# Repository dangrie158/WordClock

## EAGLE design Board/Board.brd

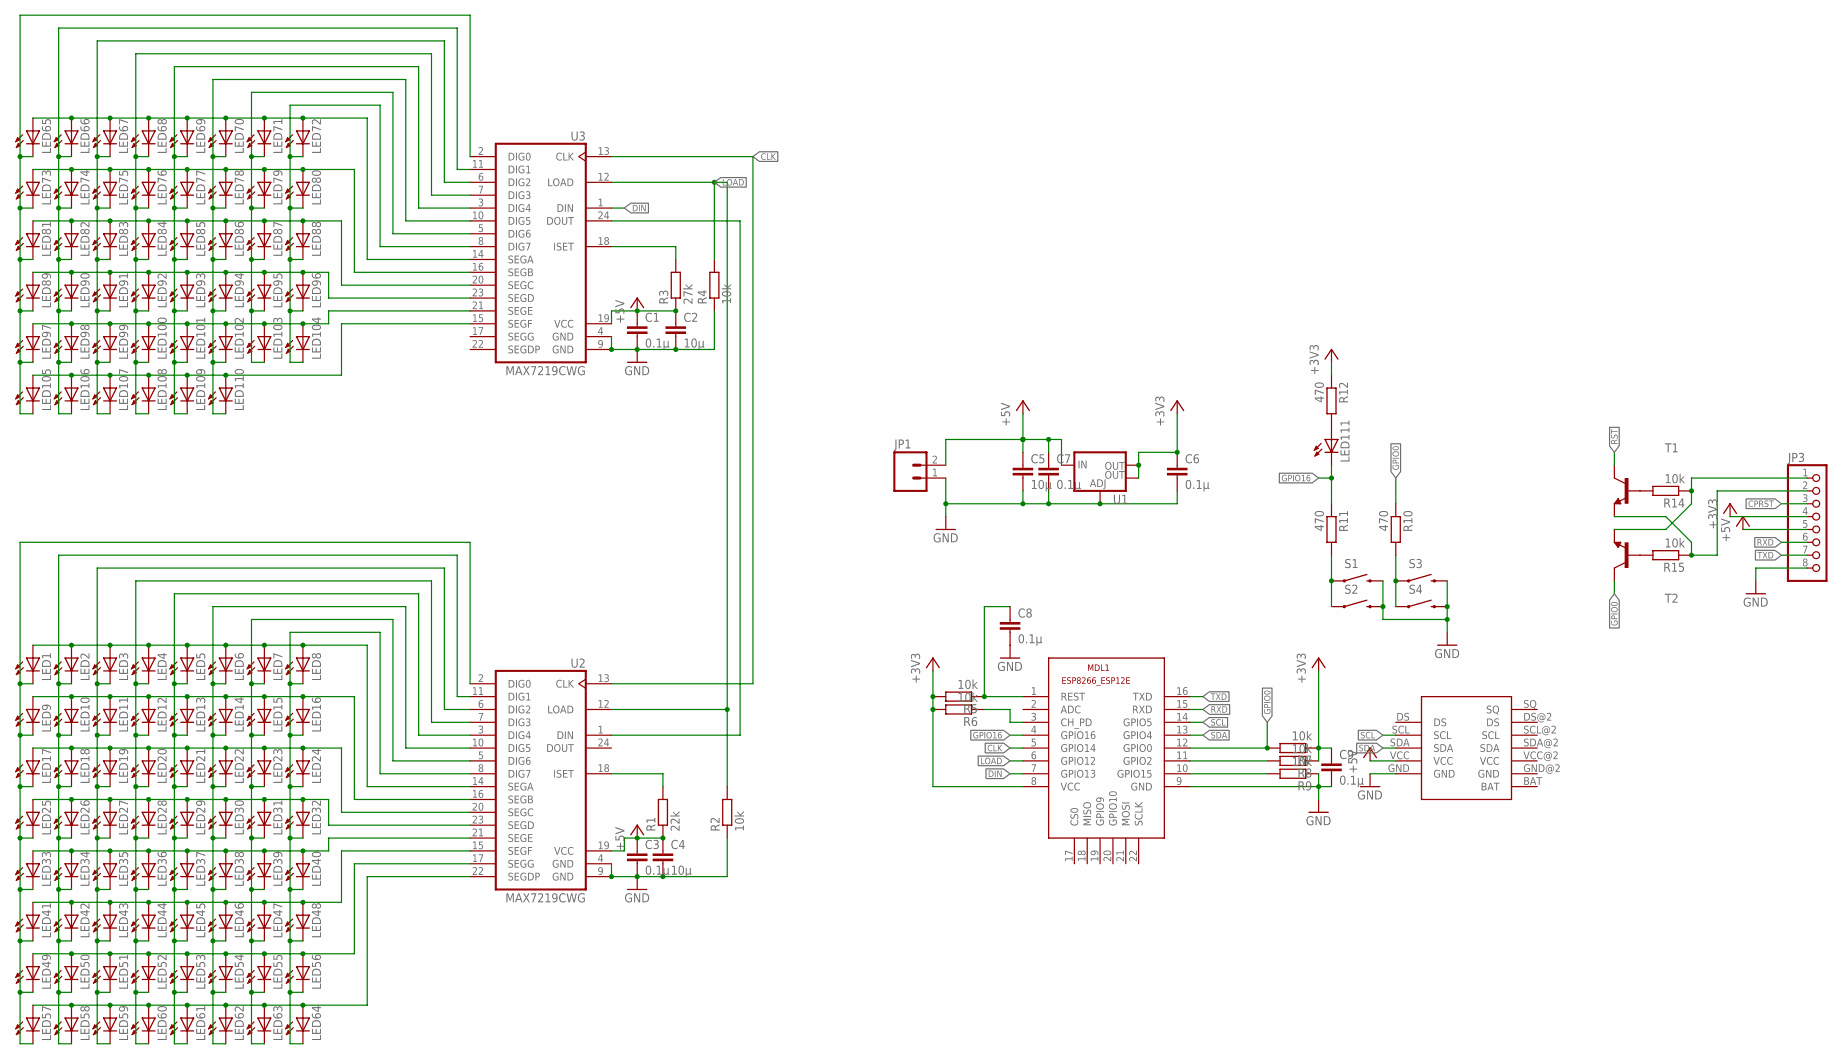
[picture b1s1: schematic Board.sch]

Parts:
C1, C3, C6, C7, C8, C9: 0.1µ; C0603
C2, C4, C5: 10µ; C0603
JP1: M02POLAR; MOLEX-1X2
JP3: PINHD-1X8; 1X08
LED1, LED2, LED3, LED4, LED5, LED6, LED7, LED8, LED9, LED10, LED11, LED12, LED13, LED14, LED15, LED16, LED17, LED18, LED19, LED20, LED21, LED22, LED23, LED24, LED25, LED26, LED27, LED28, LED29, LED30, LED31, LED32, LED33, LED34, LED35, LED36, LED37, LED38, LED39, LED40, LED41, LED42, LED43, LED44, LED45, LED46, LED47, LED48, LED49, LED50, LED51, LED52, LED53, LED54, LED55, LED56, LED57, LED58, LED59, LED60, LED61, LED62, LED63, LED64, LED65, LED66, LED67, LED68, LED69, LED70, LED71, LED72, LED73, LED74, LED75, LED76, LED77, LED78, LED79, LED80, LED81, LED82, LED83, LED84, LED85, LED86, LED87, LED88, LED89, LED90, LED91, LED92, LED93, LED94, LED95, LED96, LED97, LED98, LED99, LED100, LED101, LED102, LED103, LED104, LED105, LED106, LED107, LED108, LED109, LED110, LED111: LEDCHIPLED_0805; CHIPLED_0805
MDL1: ESP8266-12EESP8266-ESP12E; ESP8266-ESP12E
R1: 22k; R0603
R2, R4, R5, R6, R7, R8, R9, R14, R15: 10k; R0603
R3: 27k; R0603
R10, R11, R12: 470; R0603
S1, S3: SWITCH-MOMENTARY-2SIDE_EZ; TACTILE-PTH-SIDEEZ
S2, S4: SWITCH-MOMENTARY-2SMD-1101NE; TACTILE-SWITCH-1101NE
T1, T2: BC847-NPN-SOT23-BEC; SOT23-BEC
U1: V_REG_LM1117SOT223; SOT223
U2, U3: MAX7219CWG; SO24L
U$3: DS1307-MODULE

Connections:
+3V3: C6.1, C9.1, JP3.4, MDL1.8 (VCC), R5.2, R6.2, R7.1, R8.1, R12.1, U1.2 (OUT), U1.4 (OUT)
CLK: MDL1.5 (GPIO14), U2.13 (CLK), U3.13 (CLK)
DIN: MDL1.7 (GPIO13), U3.1 (DIN)
DTR: JP3.1, R14.1, T2.E
GND: C1.2, C2.2, C3.2, C4.2, C5.2, C6.2, C7.2, C8.2, C9.2, JP1.1, JP3.8, MDL1.9 (GND), R2.1, R4.1, R9.1, S1.2, S2.2, S3.2, S4.2, U1.1 (ADJ), U2.4 (GND), U2.9 (GND), U3.4 (GND), U3.9 (GND), U$3.GND
GPIO0: MDL1.12 (GPIO0), R7.2, R10.1, T2.C
GPIO16: LED111.C, MDL1.4 (GPIO16), R11.1
LOAD: MDL1.6 (GPIO12), R2.2, R4.2, U2.12 (LOAD), U3.12 (LOAD)
unnamed: LED1.C, LED9.C, LED17.C, LED25.C, LED33.C, LED41.C, LED49.C, LED57.C, U2.2 (DIG0)
unnamed: LED2.C, LED10.C, LED18.C, LED26.C, LED34.C, LED42.C, LED50.C, LED58.C, U2.11 (DIG1)
unnamed: LED9.A, LED10.A, LED11.A, LED12.A, LED13.A, LED14.A, LED15.A, LED16.A, U2.16 (SEGB)
unnamed: LED17.A, LED18.A, LED19.A, LED20.A, LED21.A, LED22.A, LED23.A, LED24.A, U2.20 (SEGC)
unnamed: LED3.C, LED11.C, LED19.C, LED27.C, LED35.C, LED43.C, LED51.C, LED59.C, U2.6 (DIG2)
unnamed: LED4.C, LED12.C, LED20.C, LED28.C, LED36.C, LED44.C, LED52.C, LED60.C, U2.7 (DIG3)
unnamed: LED5.C, LED13.C, LED21.C, LED29.C, LED37.C, LED45.C, LED53.C, LED61.C, U2.3 (DIG4)
unnamed: LED6.C, LED14.C, LED22.C, LED30.C, LED38.C, LED46.C, LED54.C, LED62.C, U2.10 (DIG5)
unnamed: LED7.C, LED15.C, LED23.C, LED31.C, LED39.C, LED47.C, LED55.C, LED63.C, U2.5 (DIG6)
unnamed: LED8.C, LED16.C, LED24.C, LED32.C, LED40.C, LED48.C, LED56.C, LED64.C, U2.8 (DIG7)
unnamed: LED1.A, LED2.A, LED3.A, LED4.A, LED5.A, LED6.A, LED7.A, LED8.A, U2.14 (SEGA)
unnamed: LED25.A, LED26.A, LED27.A, LED28.A, LED29.A, LED30.A, LED31.A, LED32.A, U2.23 (SEGD)
unnamed: LED33.A, LED34.A, LED35.A, LED36.A, LED37.A, LED38.A, LED39.A, LED40.A, U2.21 (SEGE)
unnamed: LED41.A, LED42.A, LED43.A, LED44.A, LED45.A, LED46.A, LED47.A, LED48.A, U2.15 (SEGF)
unnamed: LED49.A, LED50.A, LED51.A, LED52.A, LED53.A, LED54.A, LED55.A, LED56.A, U2.17 (SEGG)
unnamed: LED57.A, LED58.A, LED59.A, LED60.A, LED61.A, LED62.A, LED63.A, LED64.A, U2.22 (SEGDP)
unnamed: LED66.C, LED74.C, LED82.C, LED90.C, LED98.C, LED106.C, U3.11 (DIG1)
unnamed: LED65.C, LED73.C, LED81.C, LED89.C, LED97.C, LED105.C, U3.2 (DIG0)
unnamed: LED67.C, LED75.C, LED83.C, LED91.C, LED99.C, LED107.C, U3.6 (DIG2)
unnamed: LED68.C, LED76.C, LED84.C, LED92.C, LED100.C, LED108.C, U3.7 (DIG3)
unnamed: LED69.C, LED77.C, LED85.C, LED93.C, LED101.C, LED109.C, U3.3 (DIG4)
unnamed: LED70.C, LED78.C, LED86.C, LED94.C, LED102.C, LED110.C, U3.10 (DIG5)
unnamed: LED71.C, LED79.C, LED87.C, LED95.C, LED103.C, U3.5 (DIG6)
unnamed: LED72.C, LED80.C, LED88.C, LED96.C, LED104.C, U3.8 (DIG7)
unnamed: LED65.A, LED66.A, LED67.A, LED68.A, LED69.A, LED70.A, LED71.A, LED72.A, U3.14 (SEGA)
unnamed: LED73.A, LED74.A, LED75.A, LED76.A, LED77.A, LED78.A, LED79.A, LED80.A, U3.16 (SEGB)
unnamed: LED81.A, LED82.A, LED83.A, LED84.A, LED85.A, LED86.A, LED87.A, LED88.A, U3.20 (SEGC)
unnamed: LED89.A, LED90.A, LED91.A, LED92.A, LED93.A, LED94.A, LED95.A, LED96.A, U3.23 (SEGD)
unnamed: LED97.A, LED98.A, LED99.A, LED100.A, LED101.A, LED102.A, LED103.A, LED104.A, U3.21 (SEGE)
unnamed: LED105.A, LED106.A, LED107.A, LED108.A, LED109.A, LED110.A, U3.15 (SEGF)
unnamed: R10.2, S3.1, S4.1
unnamed: R14.2, T1.B
unnamed: U2.1 (DIN), U3.24 (DOUT)
unnamed: MDL1.3 (CH_PD), R6.1
unnamed: R15.2, T2.B
unnamed: LED111.A, R12.2
unnamed: MDL1.11 (GPIO2), R8.2
unnamed: R3.2, U3.18 (ISET)
unnamed: MDL1.10 (GPIO15), R9.2
unnamed: R1.2, U2.18 (ISET)
unnamed: R11.2, S1.1, S2.1
RST: C8.1, MDL1.1 (REST), R5.1, T1.C
RTS: JP3.2, R15.1, T1.E
RXD: JP3.6, MDL1.15 (RXD)
SCL: MDL1.14 (GPIO5), U$3.SCL
SDA: MDL1.13 (GPIO4), U$3.SDA
TXD: JP3.7, MDL1.16 (TXD)

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
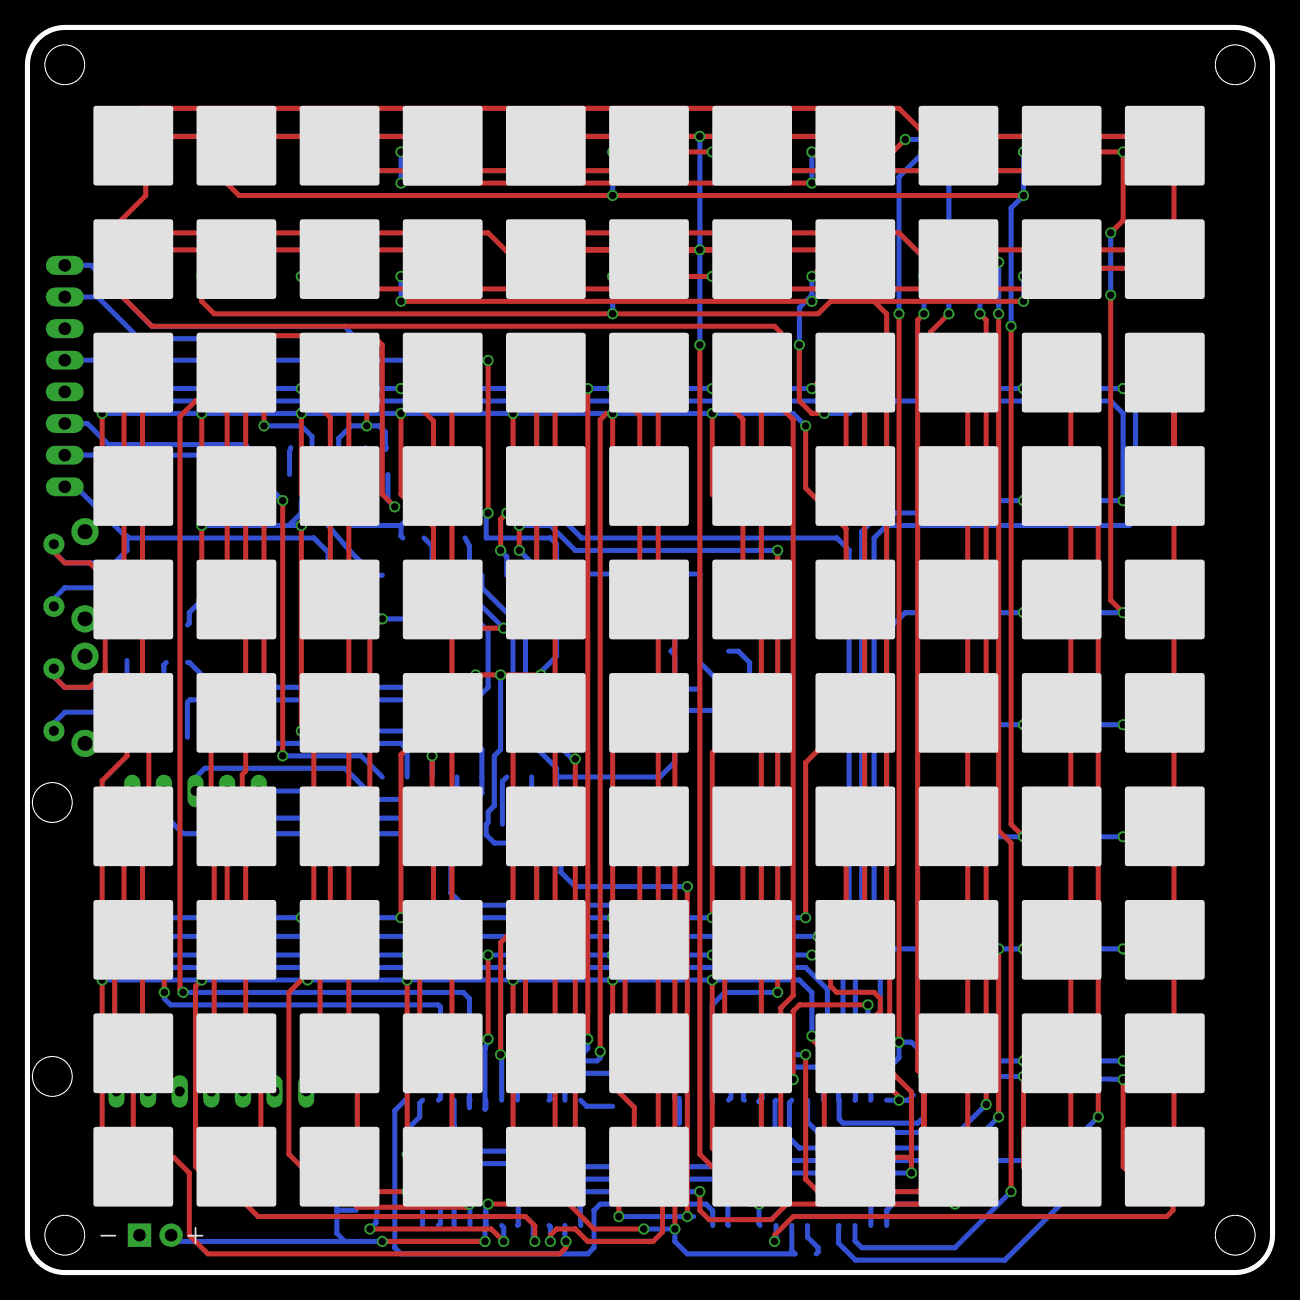
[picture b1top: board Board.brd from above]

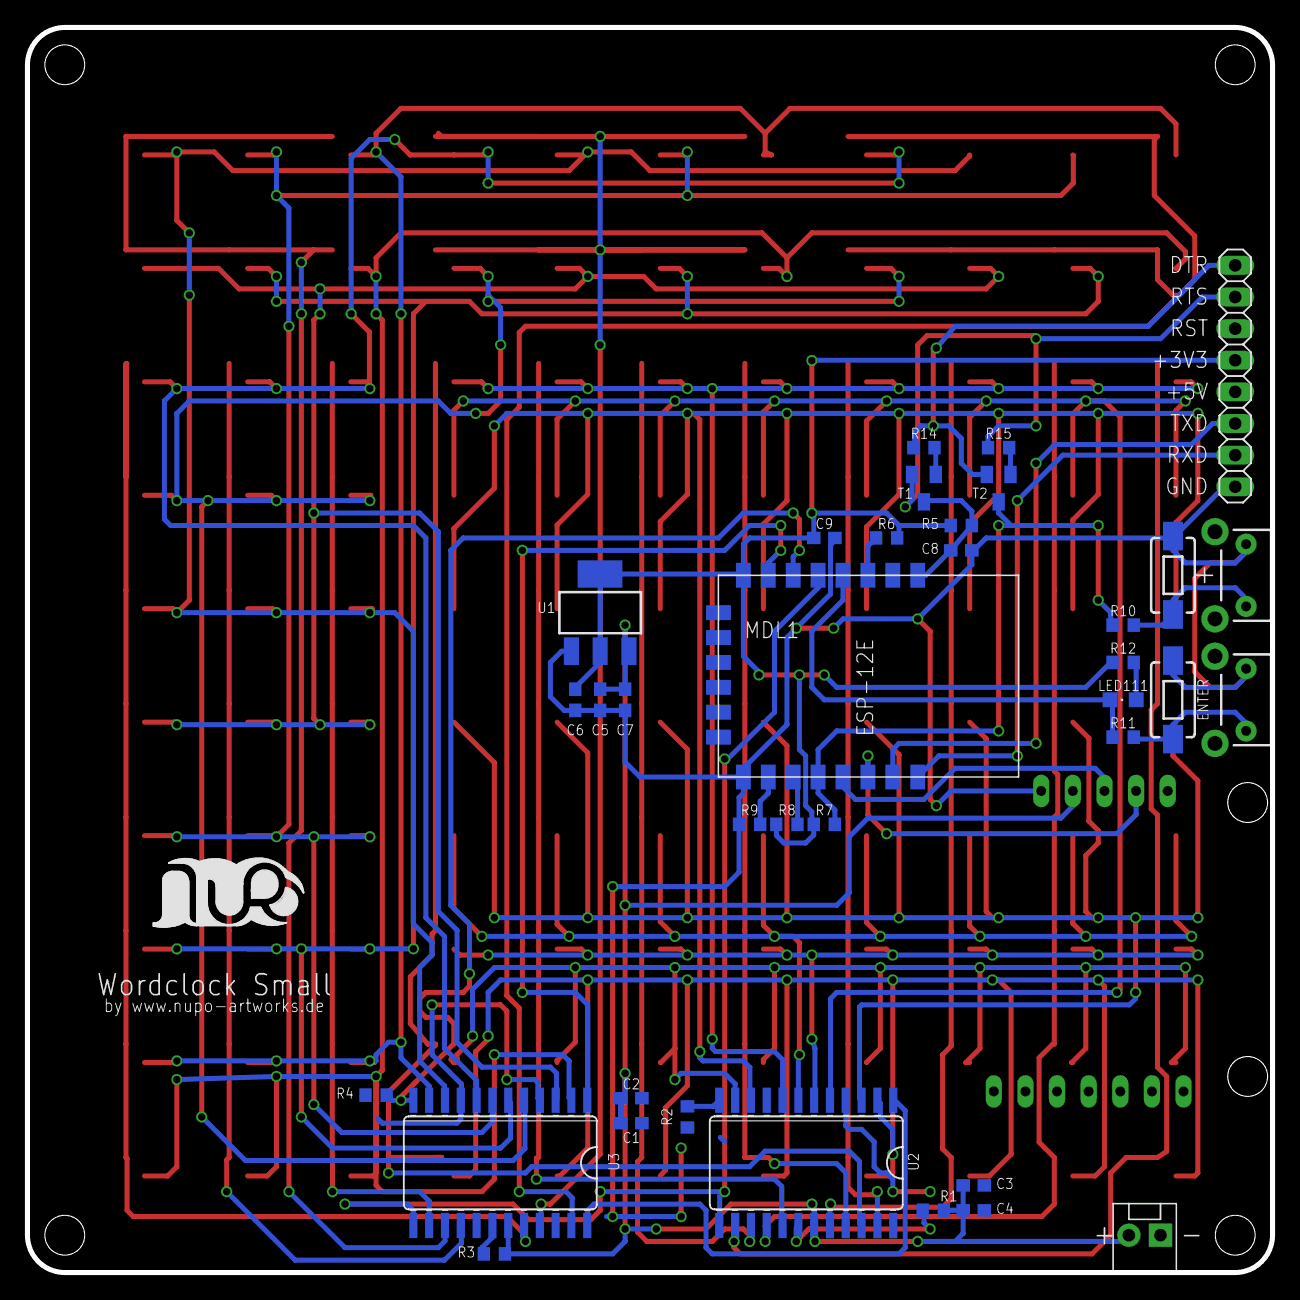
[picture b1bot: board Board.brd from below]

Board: 2 copper layers, 100.0 x 100.0 mm, 148 parts (38 on the bottom side), 56 nets.

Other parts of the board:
U$1: LOGO-SILKSCREEN

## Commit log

2016-09-05 fixed wrong footprint for MAX7219
2016-09-05 increased font size for silk screen
2016-10-09 fixed board layout issues
2016-10-09 moved board layout to subfolder
2016-10-09 added CAD files
2016-10-09 added WebSite for configuration
2016-10-09 added pio generated files to gitignore
2016-10-09 added Firmware Stub
2016-10-10 added function to display a written time

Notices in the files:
parts and their libraries:
SparkFun-PowerIC: Licensing: Creative Commons ShareAlike 4.0 International - https://creativecommons.org/licenses/by-sa/4.0
